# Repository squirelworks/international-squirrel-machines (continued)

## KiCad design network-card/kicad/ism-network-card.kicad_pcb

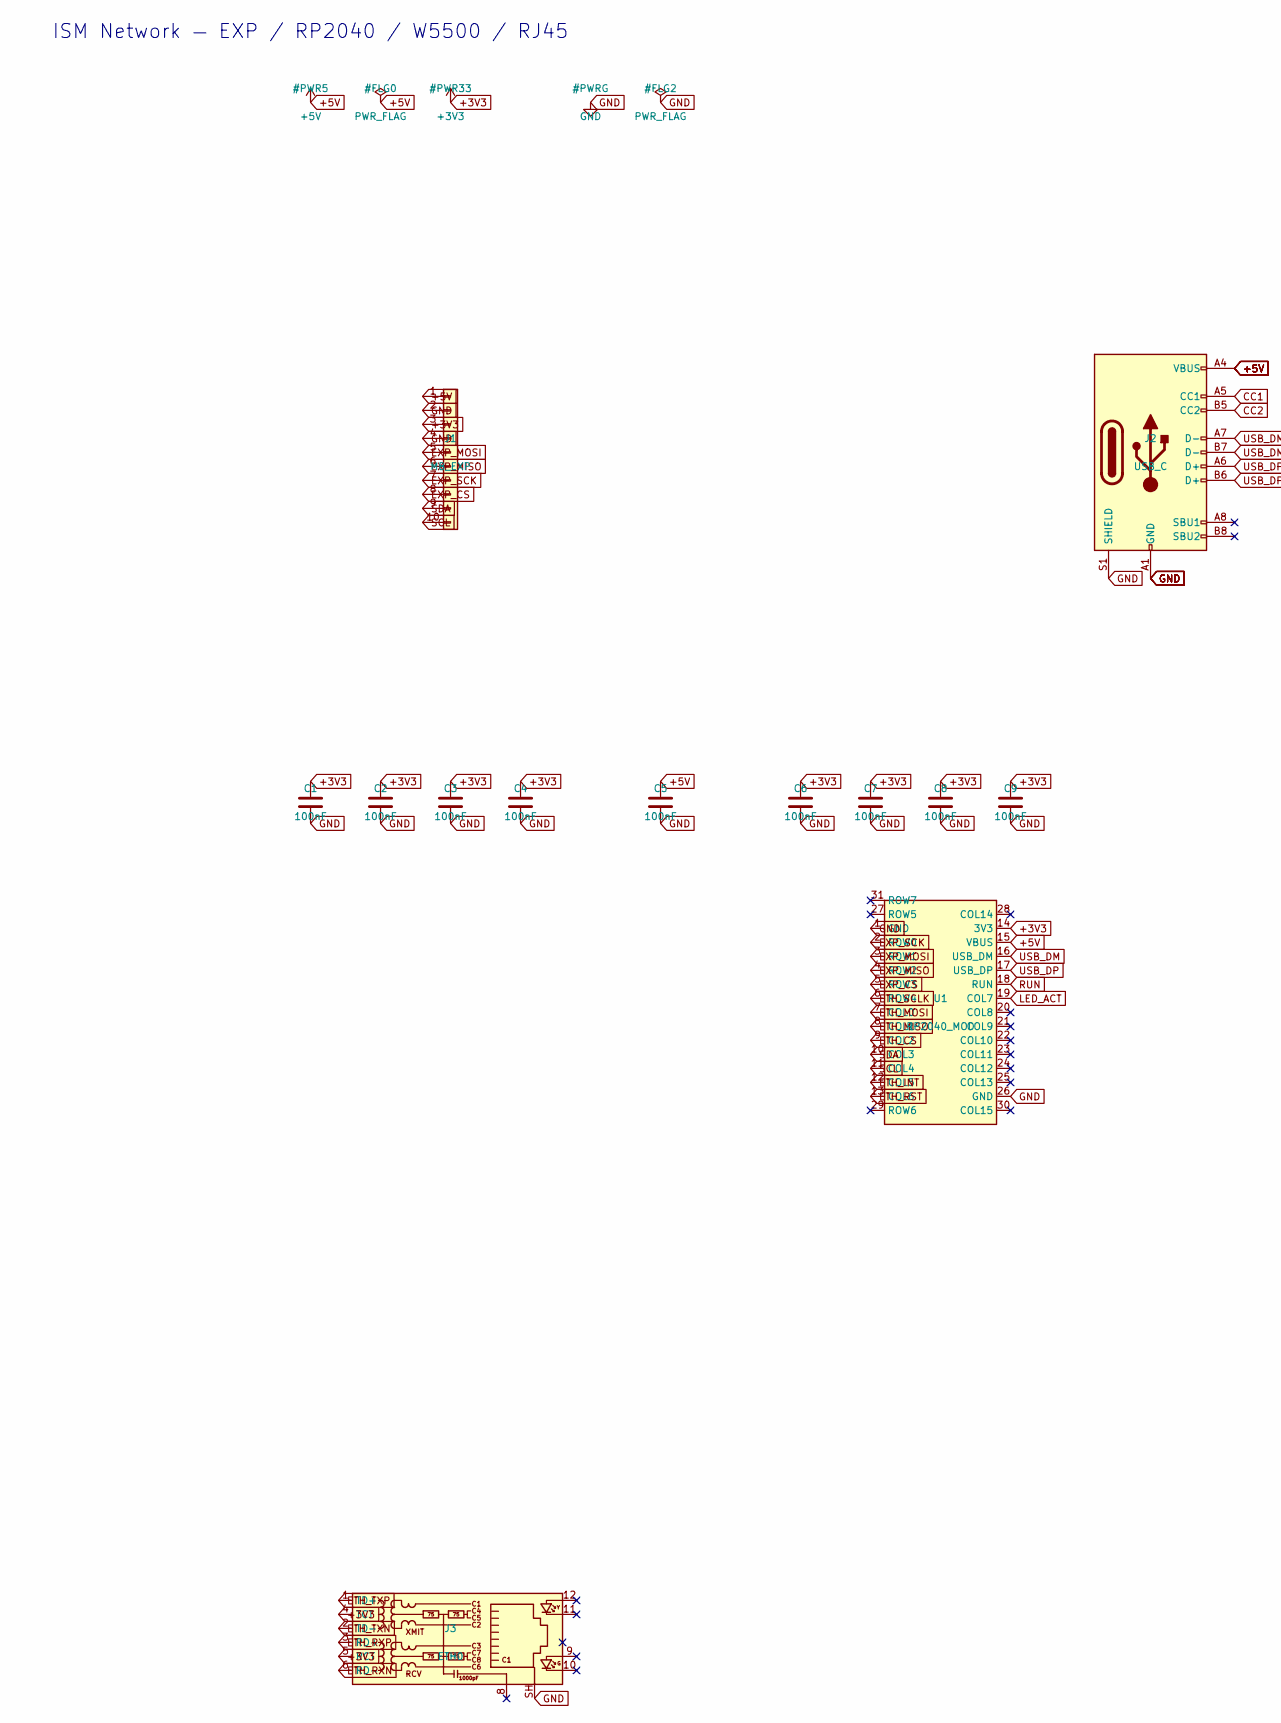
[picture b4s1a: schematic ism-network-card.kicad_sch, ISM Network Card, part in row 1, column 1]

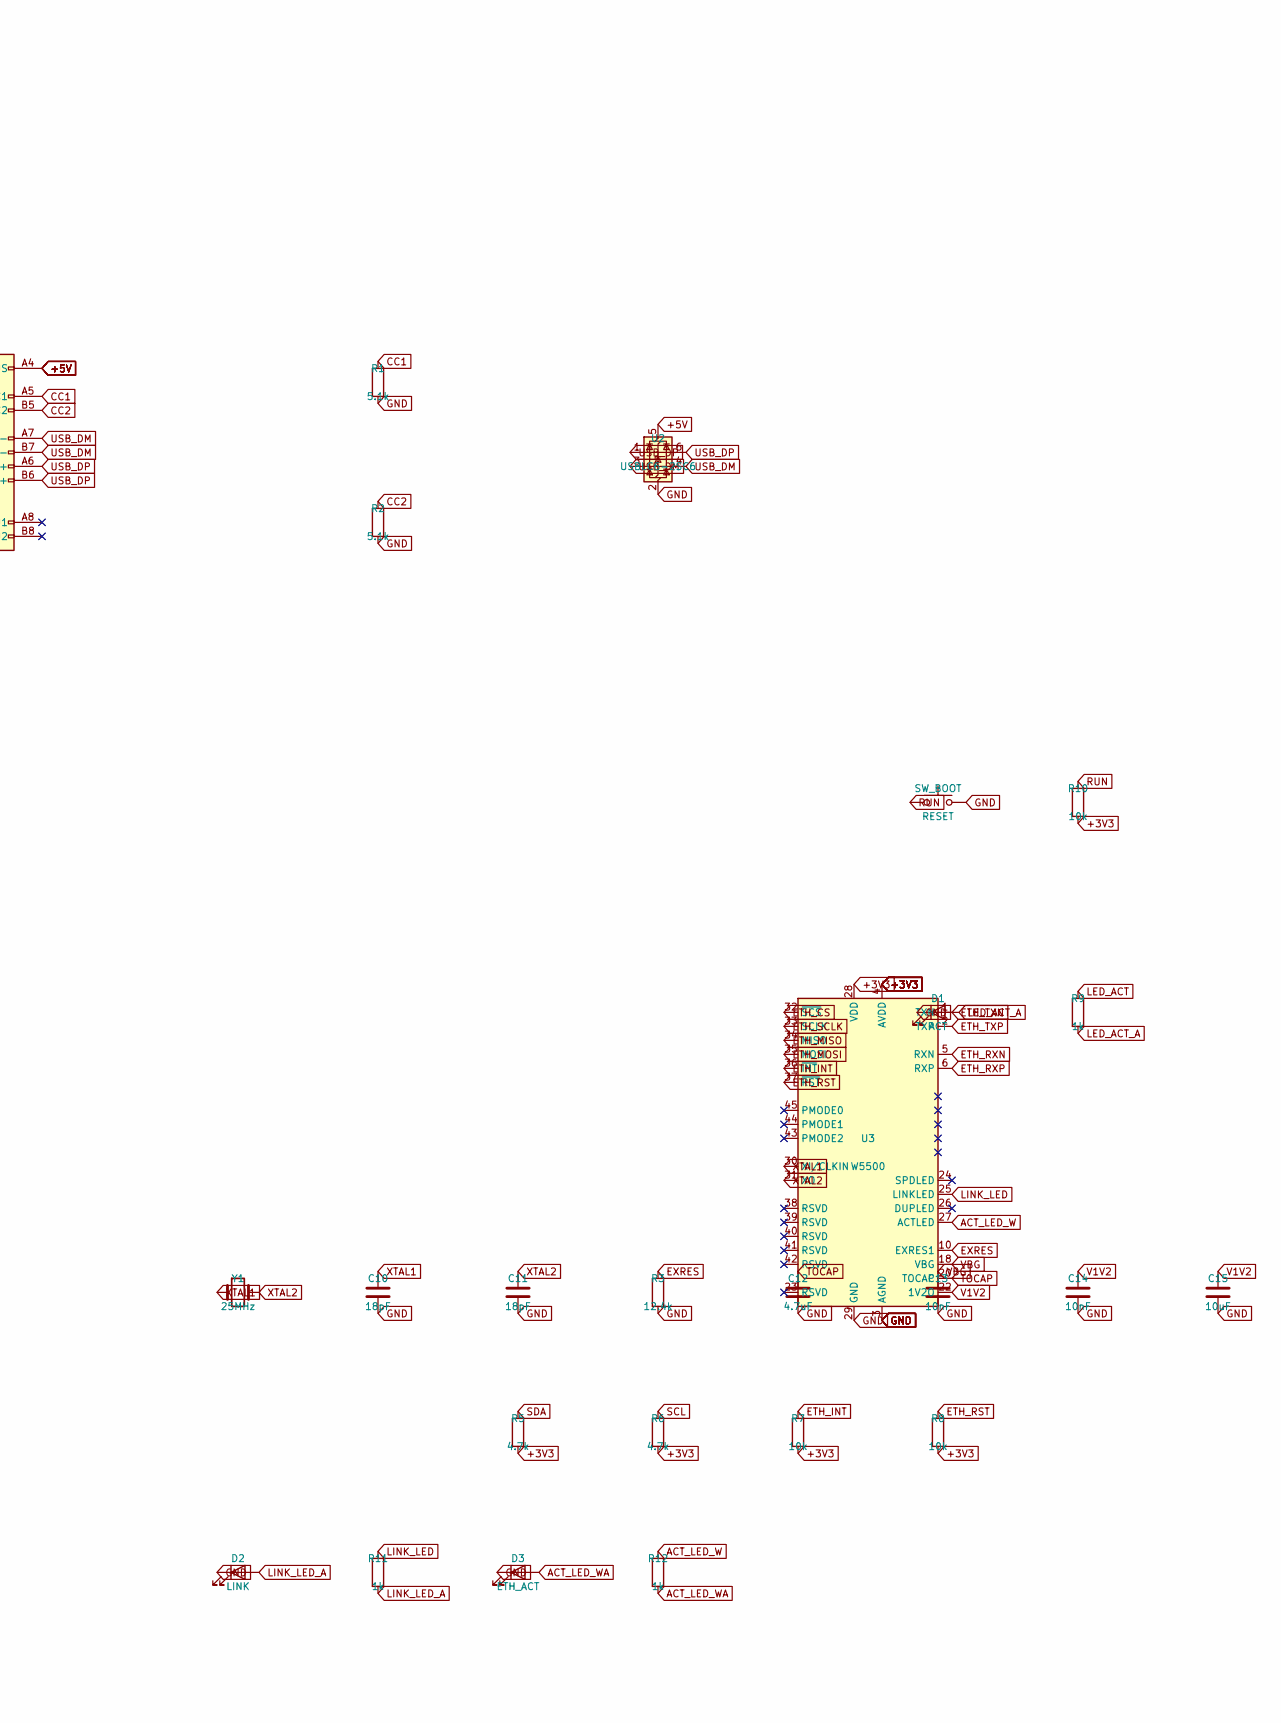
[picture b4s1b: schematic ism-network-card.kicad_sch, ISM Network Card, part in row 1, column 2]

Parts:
C1, C2, C3, C4, C5, C6, C7, C8, C9: 100nF; C_0603_1608Metric; LCSC C14663
C10, C11: 18pF; C_0603_1608Metric; LCSC C1648
C12: 4.7uF; C_0603_1608Metric; LCSC C19666
C13, C14: 10nF; C_0603_1608Metric; LCSC C1589
C15: 10uF; C_0603_1608Metric; LCSC C15850
D1: ACT; LED_0603_1608Metric; LCSC C2286
D2: LINK; LED_0603_1608Metric; LCSC C2286
D3: ETH_ACT; LED_0603_1608Metric; LCSC C2286
J1: MB_EXP; PinHeader_1x10_P2.54mm_Vertical; LCSC C124413
J2: USB_C; USB_C_Receptacle_GCT_USB4105-xx-A_16P_TopMnt_Horizontal; LCSC C165948
J3: ETH0; RJ45_Hanrun_HR911105A_Horizontal; LCSC C2839419
R1, R2: 5.1k; R_0603_1608Metric; LCSC C23244
R3: 12.4k; R_0603_1608Metric; LCSC C25905
R5, R6: 4.7k; R_0603_1608Metric; LCSC C23141
R7, R8, R10: 10k; R_0603_1608Metric; LCSC C25804
R9, R11, R12: 1k; R_0603_1608Metric; LCSC C21190
SW_BOOT: RESET; SW_SPST_PTS645; LCSC C318884
U1: RP2040_MOD; ISM_RP2040_Module; MPN ISM-RP2040-MOD
U2: USBLC6-2SC6; SOT-666; LCSC C7519
U3: W5500; LQFP-48_7x7mm_P0.5mm; MPN W5500; LCSC C113367
Y1: 25MHz; Crystal_SMD_Abracon_ABM3-2Pin_5.0x3.2mm; MPN ABM3-25.000MHZ; LCSC C9002

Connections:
+3V3: C1.1, C2.1, C3.1, C4.1, C6.1, C7.1, C8.1, C9.1, J1.3, J3.4 (TCT), J3.5 (RCT), R5.2, R6.2, R7.2, R8.2, R10.2, U1.14 (3V3), U3.4 (AVDD), U3.8 (AVDD), U3.11 (AVDD), U3.15 (AVDD), U3.17 (AVDD), U3.21 (AVDD), U3.28 (VDD)
+5V: C5.1, J1.1, J2.A4 (VBUS), J2.A9 (VBUS), J2.B4 (VBUS), J2.B9 (VBUS), U1.15 (VBUS), U2.5 (VBUS)
ACT_LED_W: R12.1, U3.27 (ACTLED)
ACT_LED_WA: D3.2 (A), R12.2
CC1: J2.A5 (CC1), R1.1
CC2: J2.B5 (CC2), R2.1
ETH_CS: U1.9 (COL2), U3.32 (~SCS)
ETH_INT: R7.1, U1.12 (COL5), U3.36 (~INT)
ETH_MISO: U1.8 (COL1), U3.34 (MISO)
ETH_MOSI: U1.7 (COL0), U3.35 (MOSI)
ETH_RST: R8.1, U1.13 (COL6), U3.37 (~RST)
ETH_RXN: J3.6 (RD-), U3.5 (RXN)
ETH_RXP: J3.3 (RD+), U3.6 (RXP)
ETH_SCLK: U1.6 (ROW4), U3.33 (SCLK)
ETH_TXN: J3.2 (TD-), U3.1 (TXN)
ETH_TXP: J3.1 (TD+), U3.2 (TXP)
EXP_CS: J1.8, U1.5 (ROW3)
EXP_MISO: J1.6, U1.4 (ROW2)
EXP_MOSI: J1.5, U1.3 (ROW1)
EXP_SCK: J1.7, U1.2 (ROW0)
EXRES: R3.1, U3.10 (EXRES1)
GND: C1.2, C2.2, C3.2, C4.2, C5.2, C6.2, C7.2, C8.2, C9.2, C10.2, C11.2, C12.2, C13.2, C14.2, C15.2, D1.1 (K), D2.1 (K), D3.1 (K), J1.2, J1.4, J2.A1 (GND), J2.A12 (GND), J2.B1 (GND), J2.B12 (GND), J2.S1 (SHIELD), J3.SH, R1.2, R2.2, R3.2, SW_BOOT.2, U1.1 (GND), U1.26 (GND), U2.2 (GND), U3.3 (AGND), U3.9 (AGND), U3.14 (AGND), U3.16 (AGND), U3.19 (AGND), U3.29 (GND), U3.48 (AGND)
LED_ACT: R9.1, U1.19 (COL7)
LED_ACT_A: D1.2 (A), R9.2
LINK_LED: R11.1, U3.25 (LINKLED)
LINK_LED_A: D2.2 (A), R11.2
RUN: R10.1, SW_BOOT.1, U1.18 (RUN)
SCL: J1.10, R6.1, U1.11 (COL4)
SDA: J1.9, R5.1, U1.10 (COL3)
TOCAP: C12.1, U3.20 (TOCAP)
USB_DM: J2.A7 (D-), J2.B7 (D-), U1.16 (USB_DM), U2.3 (I/O2), U2.4 (I/O2)
USB_DP: J2.A6 (D+), J2.B6 (D+), U1.17 (USB_DP), U2.1 (I/O1), U2.6 (I/O1)
V1V2: C14.1, C15.1, U3.22 (1V2O)
VBG: C13.1, U3.18 (VBG)
XTAL1: C10.1, U3.30 (XI/CLKIN), Y1.1
XTAL2: C11.1, U3.31 (XO), Y1.2

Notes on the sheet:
ISM Network — EXP / RP2040 / W5500 / RJ45

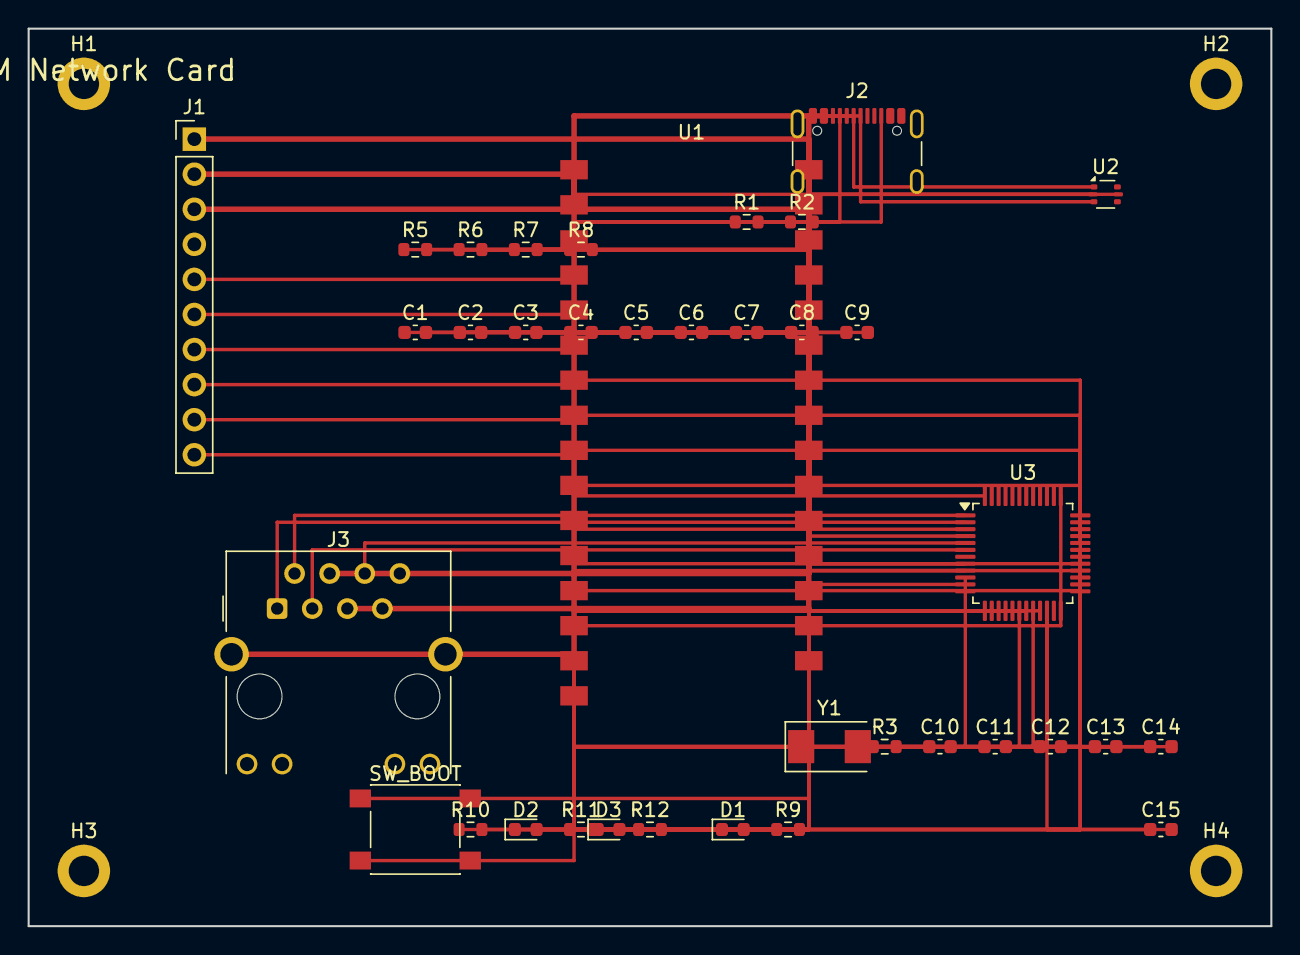
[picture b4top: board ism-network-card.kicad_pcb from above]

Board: 4 copper layers, 90.0 x 65.0 mm, 41 parts (0 on the bottom side), 36 nets.

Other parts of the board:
H1, H2, H3, H4: M2; MountingHole_2.2mm_M2_DIN965_Pad

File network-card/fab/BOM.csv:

Designator,Value,Footprint,Quantity,Manufacturer,MPN,LCSC,Notes
U1,RP2040_MOD,ISM_RP2040_Module,1,ISM,ISM-RP2040-MOD,,No LCSC — NIC controller
U2,USBLC6-2SC6,SOT-666,1,ST,USBLC6-2SC6,C7519,ESD
U3,W5500,LQFP-48,1,WIZnet,W5500,C113367,SPI Ethernet
J1,MB_EXP,PinHeader 1x10,1,,HDR-1x10,C124413,To motherboard J_EXP
J2,USB4105,GCT USB-C 16P,1,GCT,USB4105-GF-A,C165948,
J3,HR911105A,Hanrun RJ45,1,Hanrun,HR911105A,C2839419,Magnetics
Y1,25MHz,ABM3 2-pin,1,Abracon,ABM3-25.000MHZ,C9002,
"R1,R2",5.1k,0603,2,,5.1k,C23244,CC
R3,12.4k,0603,1,,12.4k,C25905,EXRES1
"R5,R6",4.7k,0603,2,,4.7k,C23141,I2C
"R7,R8,R10",10k,0603,3,,10k,C25804,
"R9,R11,R12",1k,0603,3,,1k,C21190,
C1-C9,100nF,0603,9,,100nF,C14663,
"C10,C11",18pF,0603,2,,18pF,C1648,Crystal load
C12,4.7uF,0603,1,,4.7uF,C19666,TOCAP
"C13,C14",10nF,0603,2,,10nF,C1589,
C15,10uF,0603,1,,10uF,C15850,1V2O
D1-D3,LED,0603,3,,LED,C2286,
SW_BOOT,PTS645,PTS645,1,,PTS645,C318884,
H1-H4,M2,MountingHole,4,,,,No LCSC — mechanical NPTH

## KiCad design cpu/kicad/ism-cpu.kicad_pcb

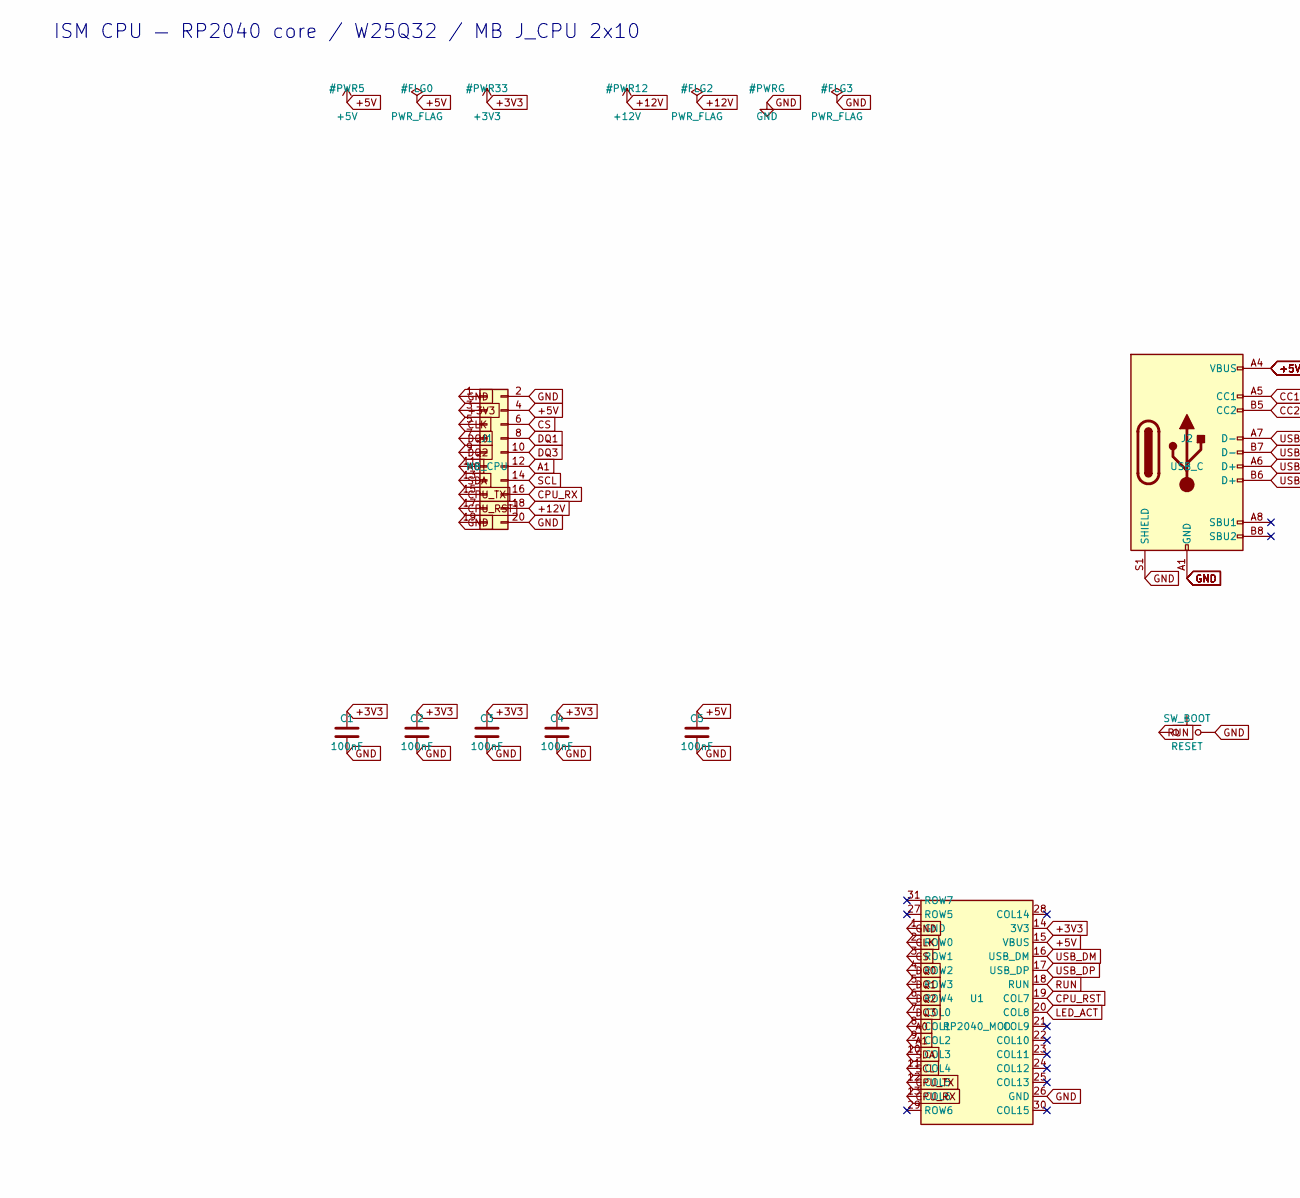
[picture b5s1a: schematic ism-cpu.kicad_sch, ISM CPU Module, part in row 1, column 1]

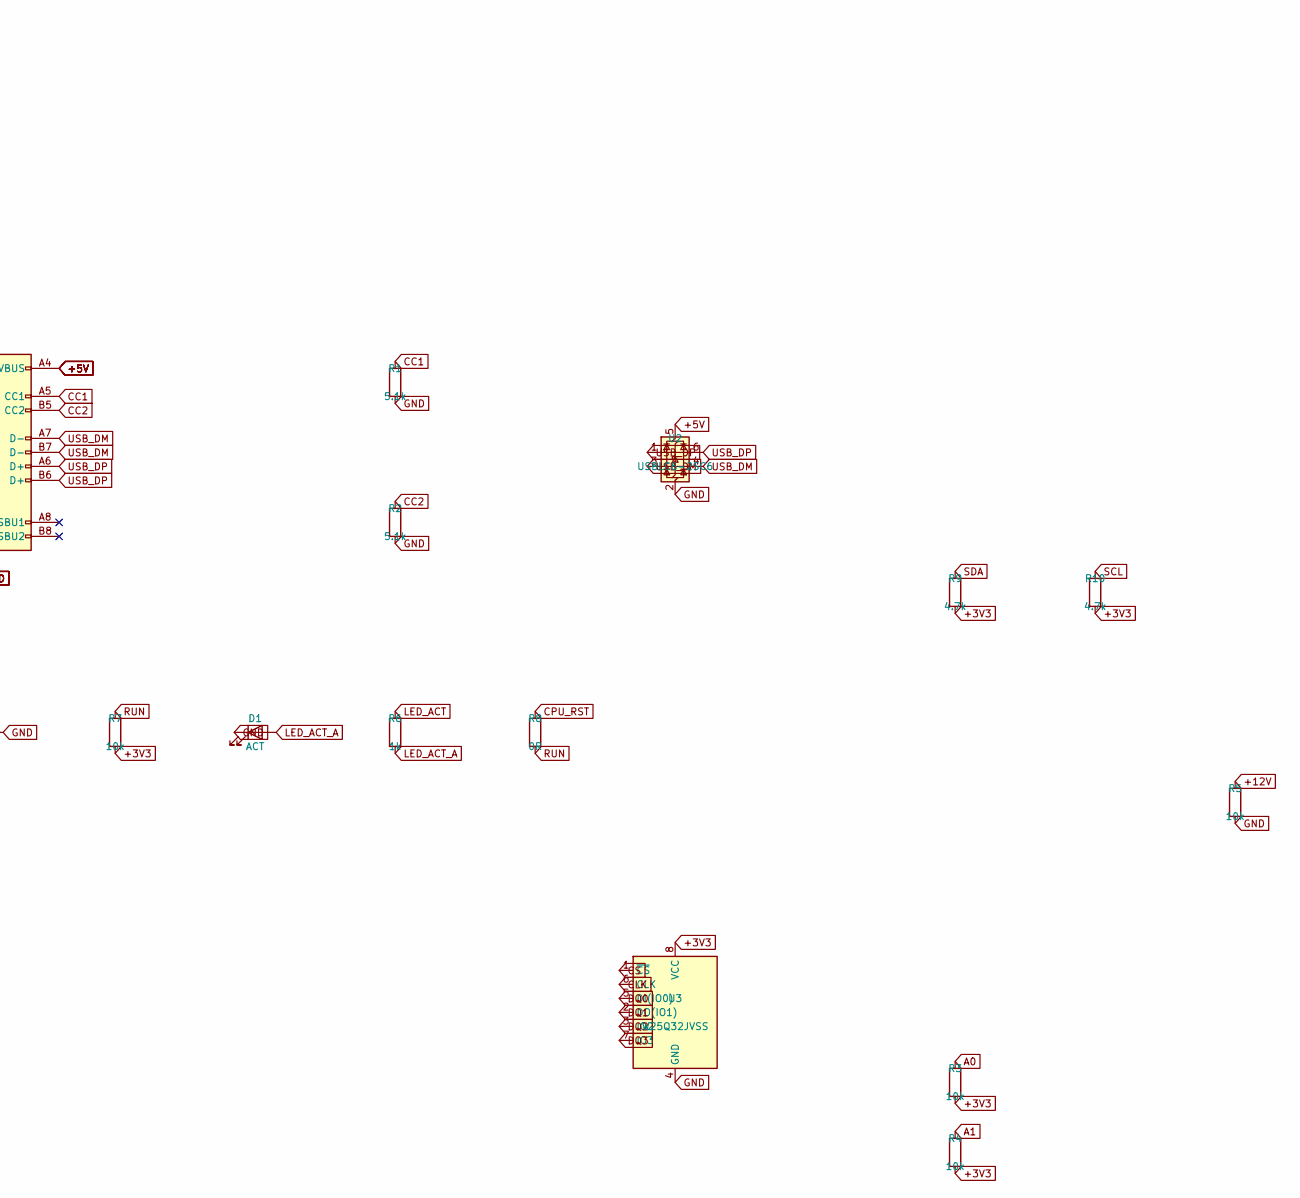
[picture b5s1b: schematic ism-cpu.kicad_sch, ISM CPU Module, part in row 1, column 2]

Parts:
C1, C2, C3, C4, C5: 100nF; C_0603_1608Metric; LCSC C14663
D1: ACT; LED_0603_1608Metric; LCSC C2286
J1: MB_CPU; PinHeader_2x10_P2.54mm_Vertical; LCSC C124384
J2: USB_C; USB_C_Receptacle_GCT_USB4105-xx-A_16P_TopMnt_Horizontal; LCSC C165948
R1, R2: 5.1k; R_0603_1608Metric; LCSC C23244
R3, R4, R5, R7: 10k; R_0603_1608Metric; LCSC C25804
R6: 1k; R_0603_1608Metric; LCSC C21190
R8: 0R; R_0603_1608Metric; LCSC C17411
R9, R10: 4.7k; R_0603_1608Metric; LCSC C23141
SW_BOOT: RESET; SW_SPST_PTS645; LCSC C318884
U1: RP2040_MOD; ISM_RP2040_Module; MPN ISM-RP2040-MOD
U2: USBLC6-2SC6; SOT-666; LCSC C7519
U3: W25Q32JVSS; SOIC-8_3.9x4.9mm_P1.27mm; MPN W25Q32JVSSIQ; LCSC C82307

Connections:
+3V3: C1.1, C2.1, C3.1, C4.1, J1.3, R3.2, R4.2, R7.2, R9.2, R10.2, U1.14 (3V3), U3.8 (VCC)
+5V: C5.1, J1.4, J2.A4 (VBUS), J2.A9 (VBUS), J2.B4 (VBUS), J2.B9 (VBUS), U1.15 (VBUS), U2.5 (VBUS)
+12V: J1.18, R5.1
A0: J1.11, R3.1, U1.8 (COL1)
A1: J1.12, R4.1, U1.9 (COL2)
CC1: J2.A5 (CC1), R1.1
CC2: J2.B5 (CC2), R2.1
CLK: J1.5, U1.2 (ROW0), U3.6 (CLK)
CPU_RST: J1.17, R8.1, U1.19 (COL7)
CPU_RX: J1.16, U1.13 (COL6)
CPU_TX: J1.15, U1.12 (COL5)
CS: J1.6, U1.3 (ROW1), U3.1 (~CS)
DQ0: J1.7, U1.4 (ROW2), U3.5 (DI(IO0))
DQ1: J1.8, U1.5 (ROW3), U3.2 (DO(IO1))
DQ2: J1.9, U1.6 (ROW4), U3.3 (IO2)
DQ3: J1.10, U1.7 (COL0), U3.7 (IO3)
GND: C1.2, C2.2, C3.2, C4.2, C5.2, D1.1 (K), J1.1, J1.2, J1.19, J1.20, J2.A1 (GND), J2.A12 (GND), J2.B1 (GND), J2.B12 (GND), J2.S1 (SHIELD), R1.2, R2.2, R5.2, SW_BOOT.2, U1.1 (GND), U1.26 (GND), U2.2 (GND), U3.4 (GND)
LED_ACT: R6.1, U1.20 (COL8)
LED_ACT_A: D1.2 (A), R6.2
RUN: R7.1, R8.2, SW_BOOT.1, U1.18 (RUN)
SCL: J1.14, R10.1, U1.11 (COL4)
SDA: J1.13, R9.1, U1.10 (COL3)
USB_DM: J2.A7 (D-), J2.B7 (D-), U1.16 (USB_DM), U2.3 (I/O2), U2.4 (I/O2)
USB_DP: J2.A6 (D+), J2.B6 (D+), U1.17 (USB_DP), U2.1 (I/O1), U2.6 (I/O1)

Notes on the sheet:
ISM CPU — RP2040 core / W25Q32 / MB J_CPU 2x10

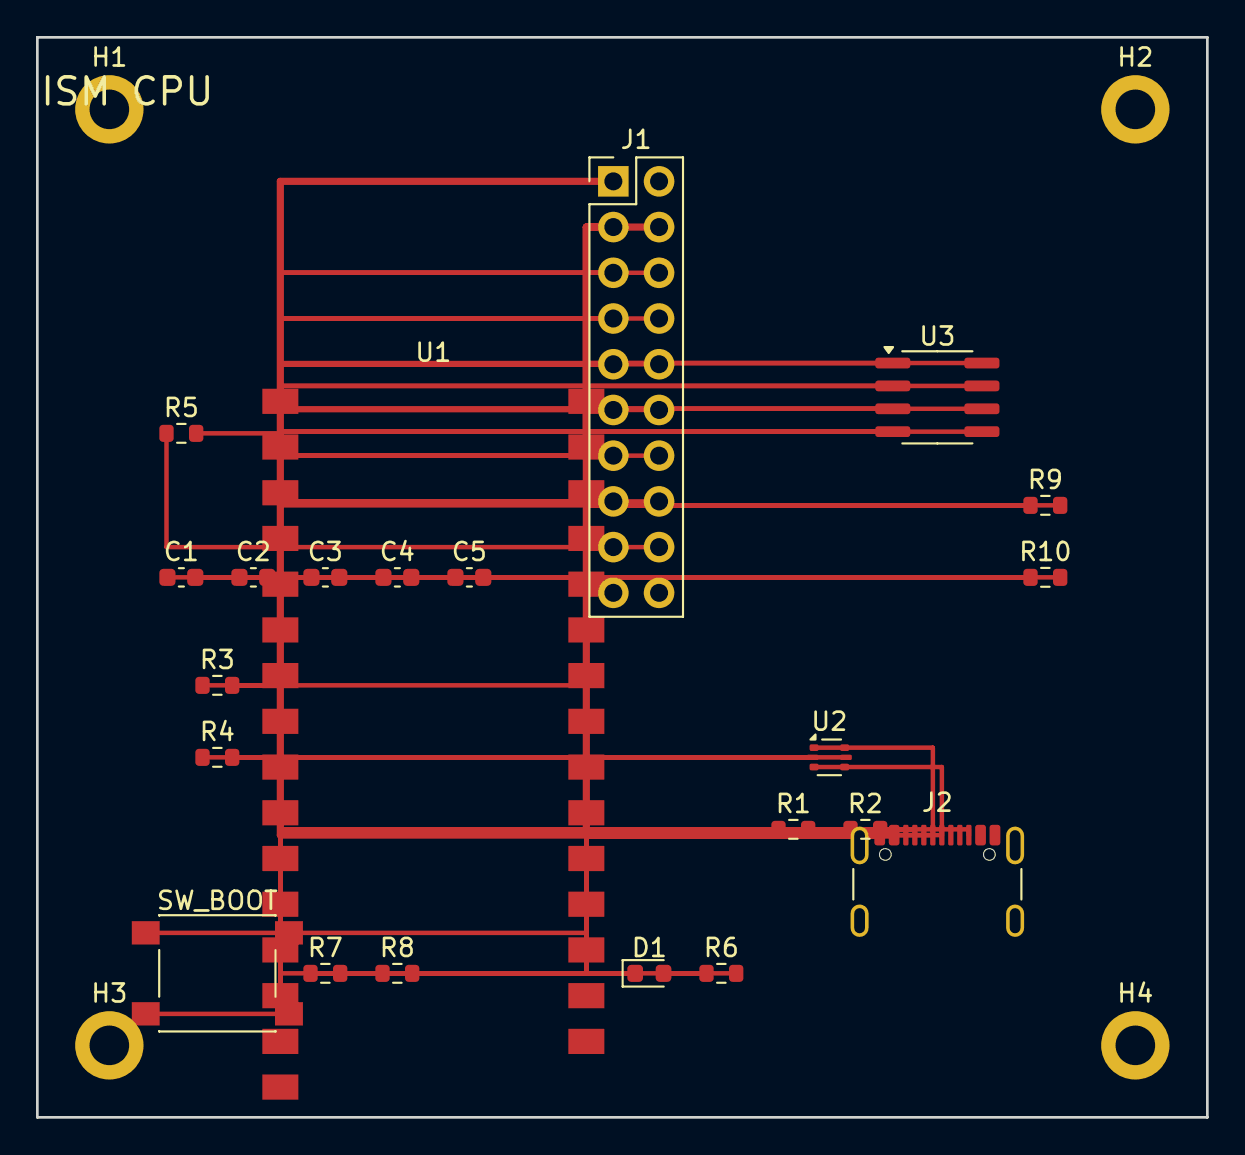
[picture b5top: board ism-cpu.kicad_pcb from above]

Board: 4 copper layers, 65.0 x 60.0 mm, 26 parts (0 on the bottom side), 24 nets.

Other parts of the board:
H1, H2, H3, H4: M2; MountingHole_2.2mm_M2_DIN965_Pad

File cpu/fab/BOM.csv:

Designator,Value,Footprint,Quantity,Manufacturer,MPN,LCSC,Notes
U1,RP2040_MOD,ISM_RP2040_Module,1,ISM,ISM-RP2040-MOD,,No LCSC — compute core
U2,USBLC6-2SC6,SOT-666,1,ST,USBLC6-2SC6,C7519,ESD
U3,W25Q32JVSS,SOIC-8,1,Winbond,W25Q32JVSSIQ,C82307,SPI flash
J1,MB_CPU,PinHeader 2x10,1,,HDR-2x10,C124384,To motherboard J_CPU
J2,USB4105,GCT USB-C 16P,1,GCT,USB4105-GF-A,C165948,
"R1,R2",5.1k,0603,2,,5.1k,C23244,CC
"R3-R5,R7",10k,0603,4,,10k,C25804,
R6,1k,0603,1,,1k,C21190,
R8,0R,0603,1,,0R,C17411,CPU_RST→RUN
"R9,R10",4.7k,0603,2,,4.7k,C23141,I2C
C1-C5,100nF,0603,5,,100nF,C14663,
D1,LED,0603,1,,LED,C2286,
SW_BOOT,PTS645,PTS645,1,,PTS645,C318884,
H1-H4,M2,MountingHole,4,,,,No LCSC — mechanical NPTH

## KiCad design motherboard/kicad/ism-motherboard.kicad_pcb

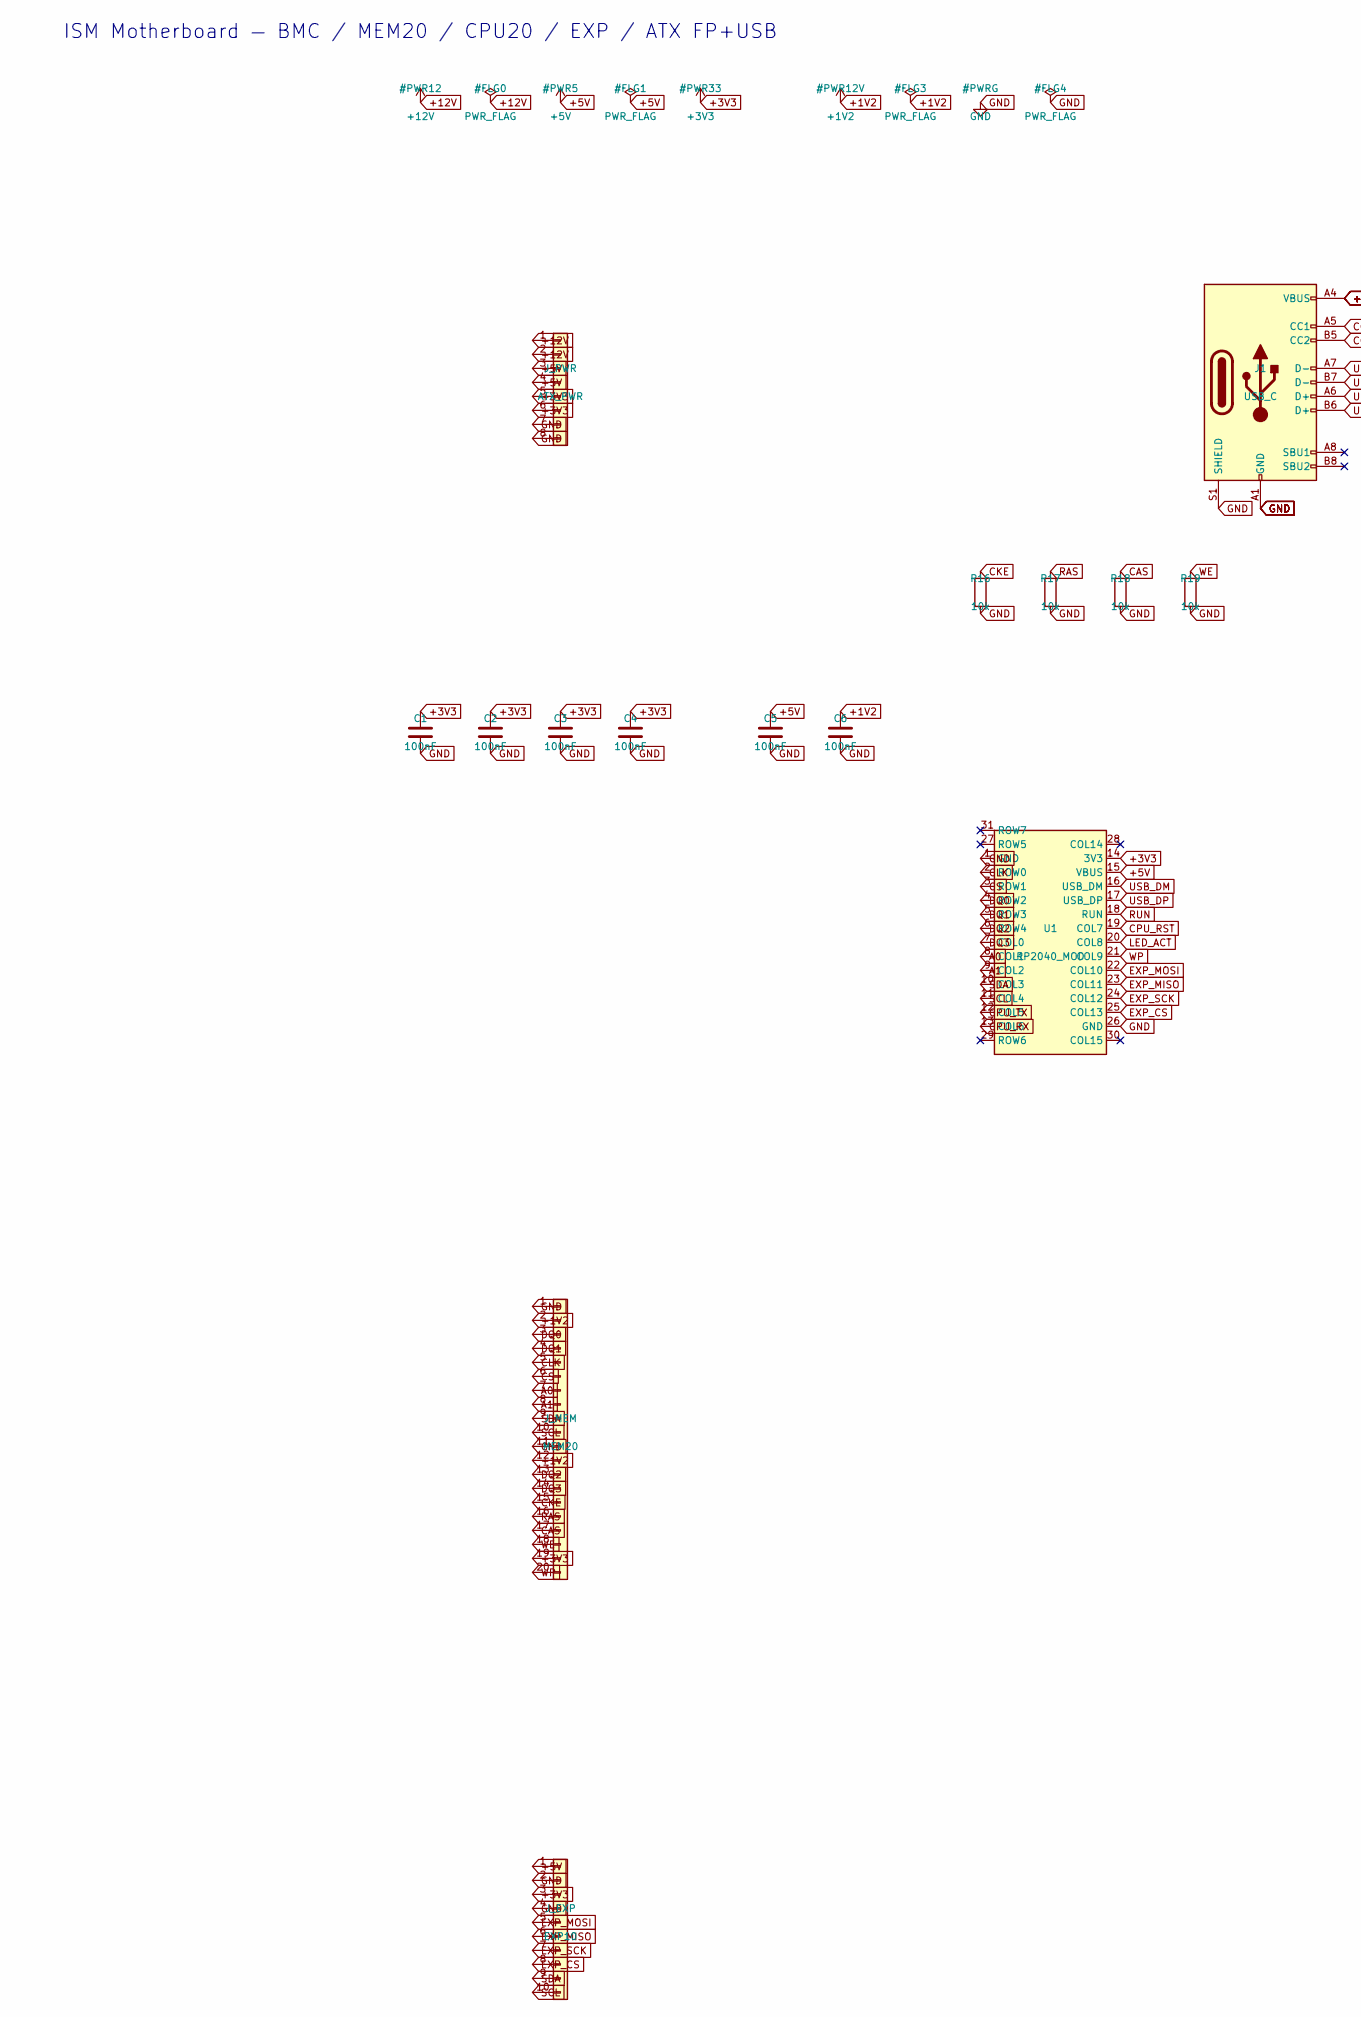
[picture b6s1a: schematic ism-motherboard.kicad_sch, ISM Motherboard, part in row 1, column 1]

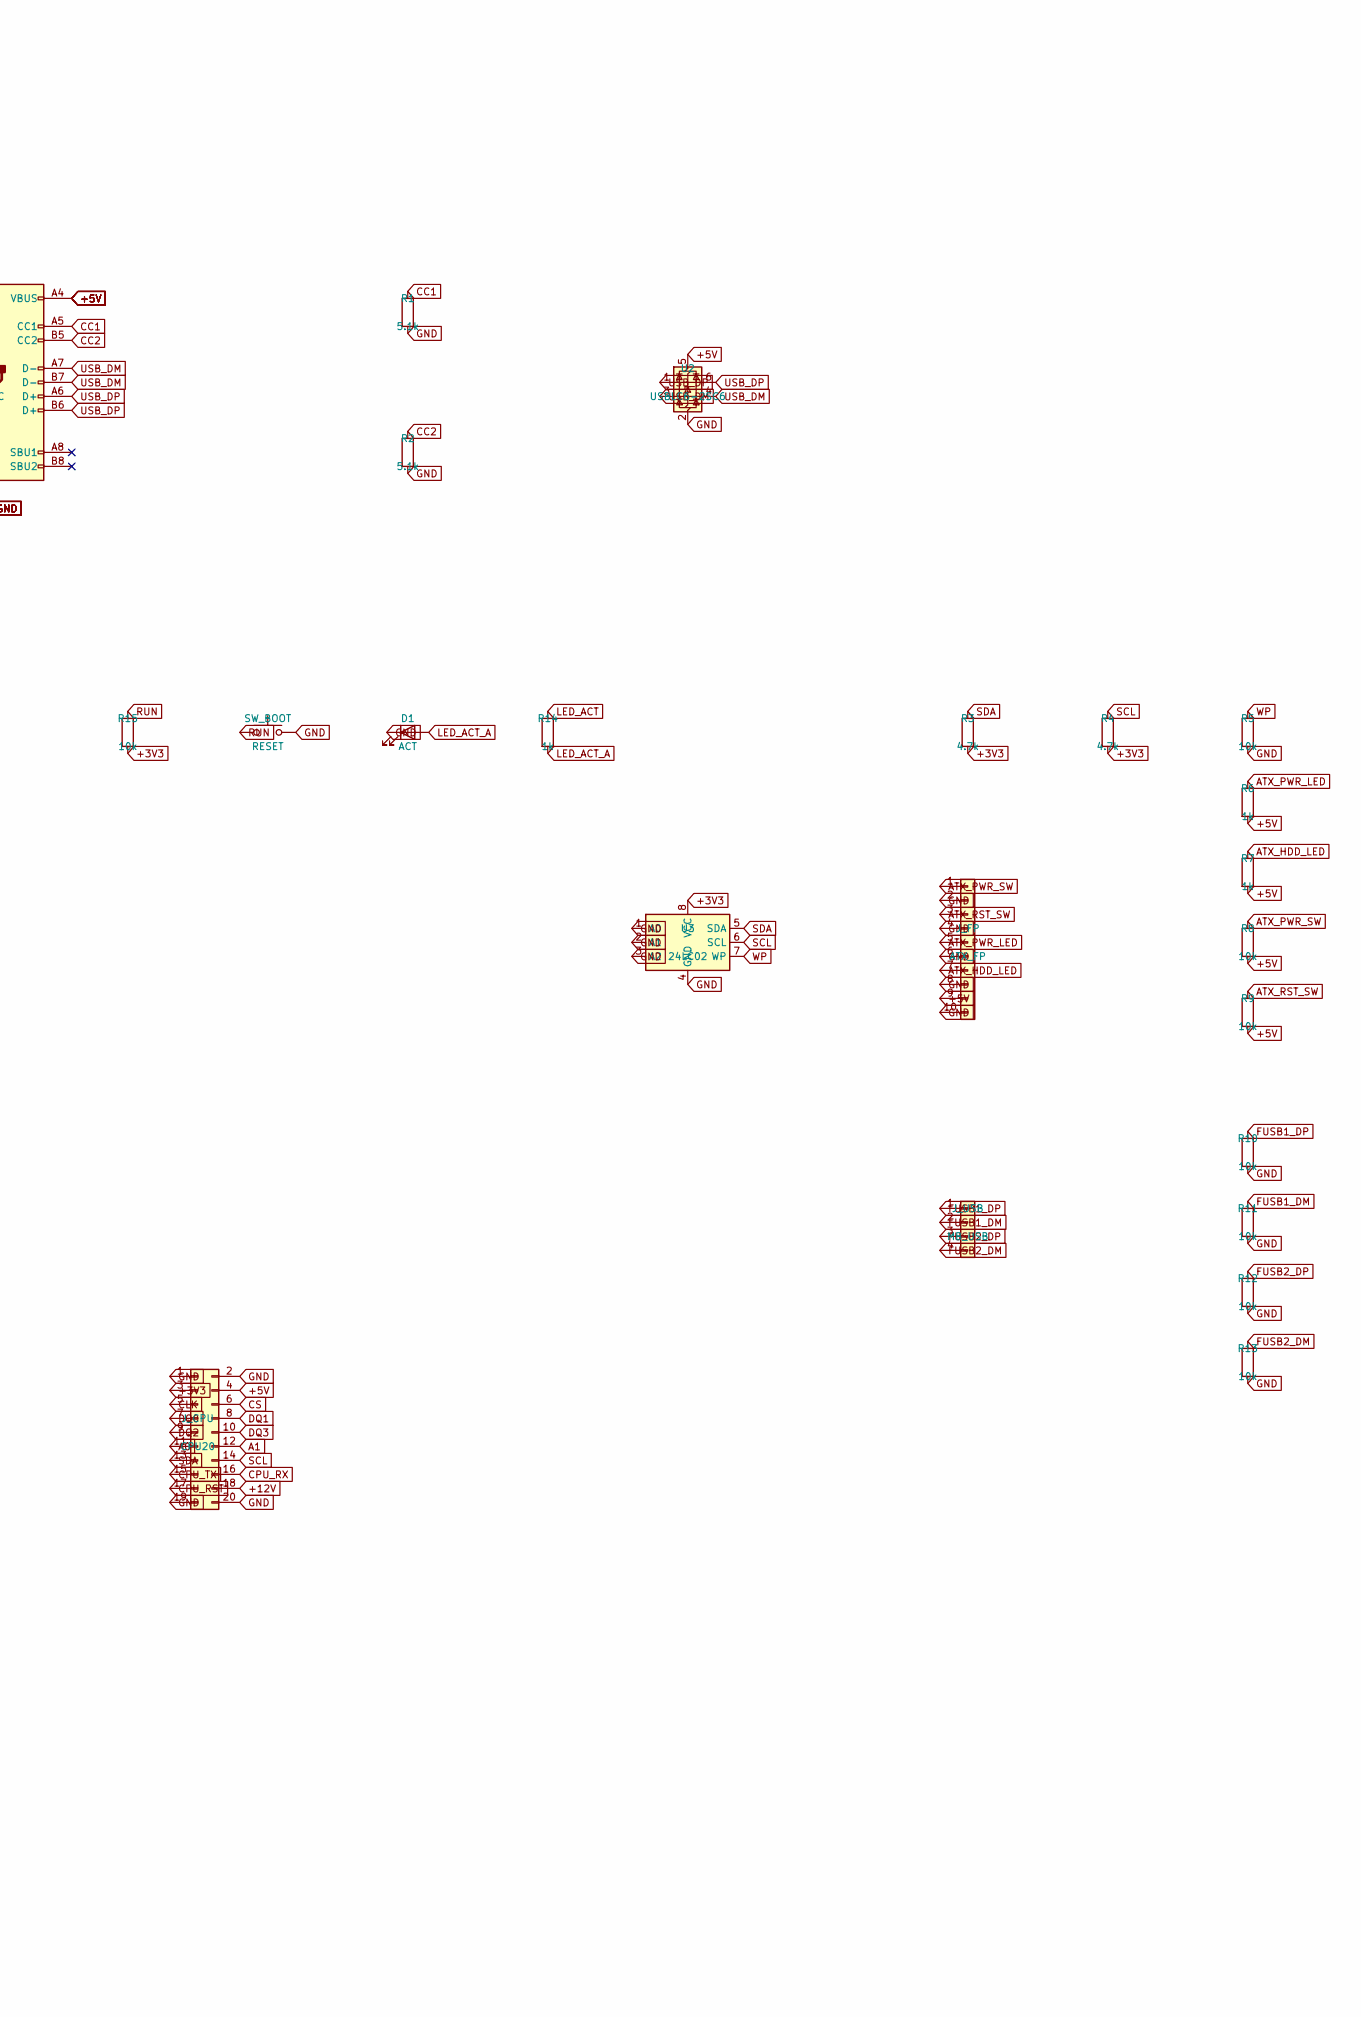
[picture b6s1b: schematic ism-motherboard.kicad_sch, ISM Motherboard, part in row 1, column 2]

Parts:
C1, C2, C3, C4, C5, C6: 100nF; C_0603_1608Metric; LCSC C14663
D1: ACT; LED_0603_1608Metric; LCSC C2286
J1: USB_C; USB_C_Receptacle_GCT_USB4105-xx-A_16P_TopMnt_Horizontal; LCSC C165948
J_CPU: CPU20; PinHeader_2x10_P2.54mm_Vertical
J_EXP: EXP10; PinHeader_1x10_P2.54mm_Vertical; LCSC C124413
J_FP: ATX_FP; PinHeader_1x10_P2.54mm_Vertical; LCSC C124413
J_MEM: MEM20; PinHeader_1x20_P2.54mm_Vertical
J_PWR: ATX_PWR; PinHeader_1x08_P2.54mm_Vertical; LCSC C124412
J_USB: MB_USB; PinHeader_1x04_P2.54mm_Vertical; LCSC C124423
R1, R2: 5.1k; R_0603_1608Metric; LCSC C23244
R3, R4: 4.7k; R_0603_1608Metric; LCSC C23141
R5, R8, R9, R10, R11, R12, R13, R15, R16, R17, R18, R19: 10k; R_0603_1608Metric; LCSC C25804
R6, R7, R14: 1k; R_0603_1608Metric; LCSC C21190
SW_BOOT: RESET; SW_SPST_PTS645; LCSC C318884
U1: RP2040_MOD; ISM_RP2040_Module; MPN ISM-RP2040-MOD
U2: USBLC6-2SC6; SOT-666; LCSC C7519
U3: 24LC02; SOIC-8_3.9x4.9mm_P1.27mm; MPN 24LC02B; LCSC C7500

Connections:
+1V2: C6.1, J_MEM.2, J_MEM.12
+3V3: C1.1, C2.1, C3.1, C4.1, J_CPU.3, J_EXP.3, J_MEM.19, J_PWR.5, J_PWR.6, R3.2, R4.2, R15.2, U1.14 (3V3), U3.8 (VCC)
+5V: C5.1, J1.A4 (VBUS), J1.A9 (VBUS), J1.B4 (VBUS), J1.B9 (VBUS), J_CPU.4, J_EXP.1, J_FP.9, J_PWR.3, J_PWR.4, R6.2, R7.2, R8.2, R9.2, U1.15 (VBUS), U2.5 (VBUS)
+12V: J_CPU.18, J_PWR.1, J_PWR.2
A0: J_CPU.11, J_MEM.7, U1.8 (COL1)
A1: J_CPU.12, J_MEM.8, U1.9 (COL2)
ATX_HDD_LED: J_FP.7, R7.1
ATX_PWR_LED: J_FP.5, R6.1
ATX_PWR_SW: J_FP.1, R8.1
ATX_RST_SW: J_FP.3, R9.1
CAS: J_MEM.17, R18.1
CC1: J1.A5 (CC1), R1.1
CC2: J1.B5 (CC2), R2.1
CKE: J_MEM.15, R16.1
CLK: J_CPU.5, J_MEM.5, U1.2 (ROW0)
CPU_RST: J_CPU.17, U1.19 (COL7)
CPU_RX: J_CPU.16, U1.13 (COL6)
CPU_TX: J_CPU.15, U1.12 (COL5)
CS: J_CPU.6, J_MEM.6, U1.3 (ROW1)
DQ0: J_CPU.7, J_MEM.3, U1.4 (ROW2)
DQ1: J_CPU.8, J_MEM.4, U1.5 (ROW3)
DQ2: J_CPU.9, J_MEM.13, U1.6 (ROW4)
DQ3: J_CPU.10, J_MEM.14, U1.7 (COL0)
EXP_CS: J_EXP.8, U1.25 (COL13)
EXP_MISO: J_EXP.6, U1.23 (COL11)
EXP_MOSI: J_EXP.5, U1.22 (COL10)
EXP_SCK: J_EXP.7, U1.24 (COL12)
FUSB1_DM: J_USB.2, R11.1
FUSB1_DP: J_USB.1, R10.1
FUSB2_DM: J_USB.4, R13.1
FUSB2_DP: J_USB.3, R12.1
GND: C1.2, C2.2, C3.2, C4.2, C5.2, C6.2, D1.1 (K), J1.A1 (GND), J1.A12 (GND), J1.B1 (GND), J1.B12 (GND), J1.S1 (SHIELD), J_CPU.1, J_CPU.2, J_CPU.19, J_CPU.20, J_EXP.2, J_EXP.4, J_FP.2, J_FP.4, J_FP.6, J_FP.8, J_FP.10, J_MEM.1, J_MEM.11, J_PWR.7, J_PWR.8, R1.2, R2.2, R5.2, R10.2, R11.2, R12.2, R13.2, R16.2, R17.2, R18.2, R19.2, SW_BOOT.2, U1.1 (GND), U1.26 (GND), U2.2 (GND), U3.1 (A0), U3.2 (A1), U3.3 (A2), U3.4 (GND)
LED_ACT: R14.1, U1.20 (COL8)
LED_ACT_A: D1.2 (A), R14.2
RAS: J_MEM.16, R17.1
RUN: R15.1, SW_BOOT.1, U1.18 (RUN)
SCL: J_CPU.14, J_EXP.10, J_MEM.10, R4.1, U1.11 (COL4), U3.6 (SCL)
SDA: J_CPU.13, J_EXP.9, J_MEM.9, R3.1, U1.10 (COL3), U3.5 (SDA)
USB_DM: J1.A7 (D-), J1.B7 (D-), U1.16 (USB_DM), U2.3 (I/O2), U2.4 (I/O2)
USB_DP: J1.A6 (D+), J1.B6 (D+), U1.17 (USB_DP), U2.1 (I/O1), U2.6 (I/O1)
WE: J_MEM.18, R19.1
WP: J_MEM.20, R5.1, U1.21 (COL9), U3.7 (WP)

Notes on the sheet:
ISM Motherboard — BMC / MEM20 / CPU20 / EXP / ATX FP+USB
